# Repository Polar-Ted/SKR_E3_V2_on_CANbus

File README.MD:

# SKR Mini E3 V2 on CANBUS

Wiring and config to run the SKR Mini E3 V2 over CAN

## Setup Steps

### Compile Toolboard Firmware
- ssh to your pi console
- CD to the klipper directory
```
cd klipper
```
- Run MAKE Clean
```
make clean
```
- open menuconfig
```
make menuconfig
```
- Set the following options for CANBUS connection  
    Note: If you already have a CAN implementation set the CANBUS speed to match your existing configuration. Common speeds are 250000 and 500000

-Run make
```
make
```
-When the make is complete connect to the klipper host with SFTP and 
navigate to the Klipper out file
```
 /home/pi/klipper/out
```
- Copy the Klipper.bin file to your local machine 
- Rename the file to firmware.bin
- Transfer firmware.bin to your microSD card
- Replace the microSD card into the Mini E3.
- Power on the system. SKR will automatically update with the Klipper firmware.

## Wiring Diagram

    Note: The MCP2551 does not have 120 ohm resistors. If this is the only device on your CANBUS you will need to wire a 120 ohm resistor between CANH and CANL at the MCP2551 connector.  You CANBUS should measure 60 ohms between CAN H and CAN L with all the devices connected. ( measure while powered off) 

## Links  

  [MCP2551 board](https://www.aliexpress.com/item/2255800362518857.html?spm=a2g0o.order_list.0.0.21ef1802WJAiGd)
  
  [SKR Mini E3 V2](https://github.com/bigtreetech/BIGTREETECH-SKR-mini-E3/tree/master/hardware/BTT%20SKR%20MINI%20E3%20V2.0/Hardware)
  
  [Maz0r CanBus Configuratuion and troubleshooting guides](https://maz0r.github.io/klipper_canbus/)
  
  [rootiest guide to SKR Pico as a USB Can bridge](https://github.com/rootiest/zippy-klipper_config/blob/master/guides/Guide-pico_can.md)

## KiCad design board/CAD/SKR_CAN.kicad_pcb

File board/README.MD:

## Project to create a plug in CAN board for the EXP1 socket on the SKR Mini E3 V2 and V3.        ##

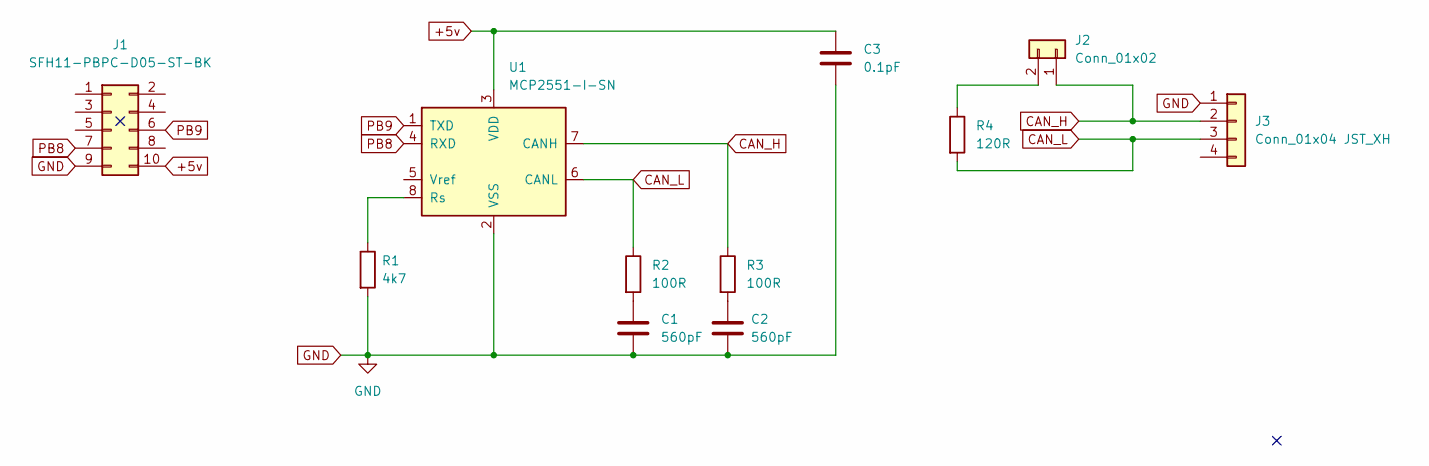
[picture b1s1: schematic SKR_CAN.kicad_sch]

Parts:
C1, C2: 560pF; C_0805_2012Metric_Pad1.18x1.45mm_HandSolder
C3: 0.1pF; C_0805_2012Metric_Pad1.18x1.45mm_HandSolder
J1: SFH11-PBPC-D05-ST-BK; PinHeader_2x05_P2.54mm_Vertical
J2: Conn_01x02; PinHeader_1x02_P2.54mm_Vertical
J3: Conn_01x04 JST_XH; JST_XH_B4B-XH-A_1x04_P2.50mm_Vertical
R1: 4k7; R_0805_2012Metric_Pad1.20x1.40mm_HandSolder
R2, R3: 100R; R_0805_2012Metric_Pad1.20x1.40mm_HandSolder
R4: 120R; R_0805_2012Metric_Pad1.20x1.40mm_HandSolder
U1: MCP2551-I-SN; SOIC-8_3.9x4.9mm_P1.27mm

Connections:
+5v: C3.1, J1.10, U1.3 (VDD)
CAN_H: J2.1, J3.2, R3.1, U1.7 (CANH)
CAN_L: J3.3, R2.1, R4.2, U1.6 (CANL)
GND: C1.2, C2.2, C3.2, J1.9, J3.1, R1.2, U1.2 (VSS)
unnamed: C1.1, R2.2
unnamed: C2.1, R3.2
unnamed: J2.2, R4.1
unnamed: R1.1, U1.8 (Rs)
PB8: J1.7, U1.4 (RXD)
PB9: J1.6, U1.1 (TXD)

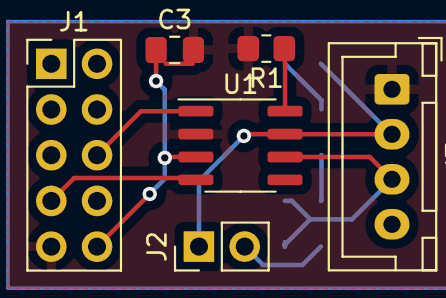
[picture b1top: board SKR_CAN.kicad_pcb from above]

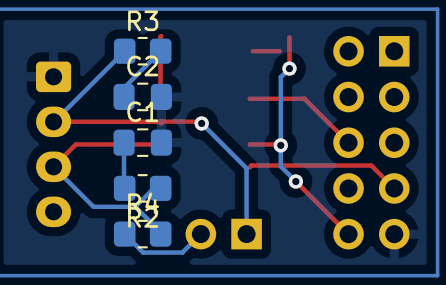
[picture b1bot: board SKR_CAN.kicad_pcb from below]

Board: 2 copper layers, 11 parts (5 on the bottom side), 10 nets.
